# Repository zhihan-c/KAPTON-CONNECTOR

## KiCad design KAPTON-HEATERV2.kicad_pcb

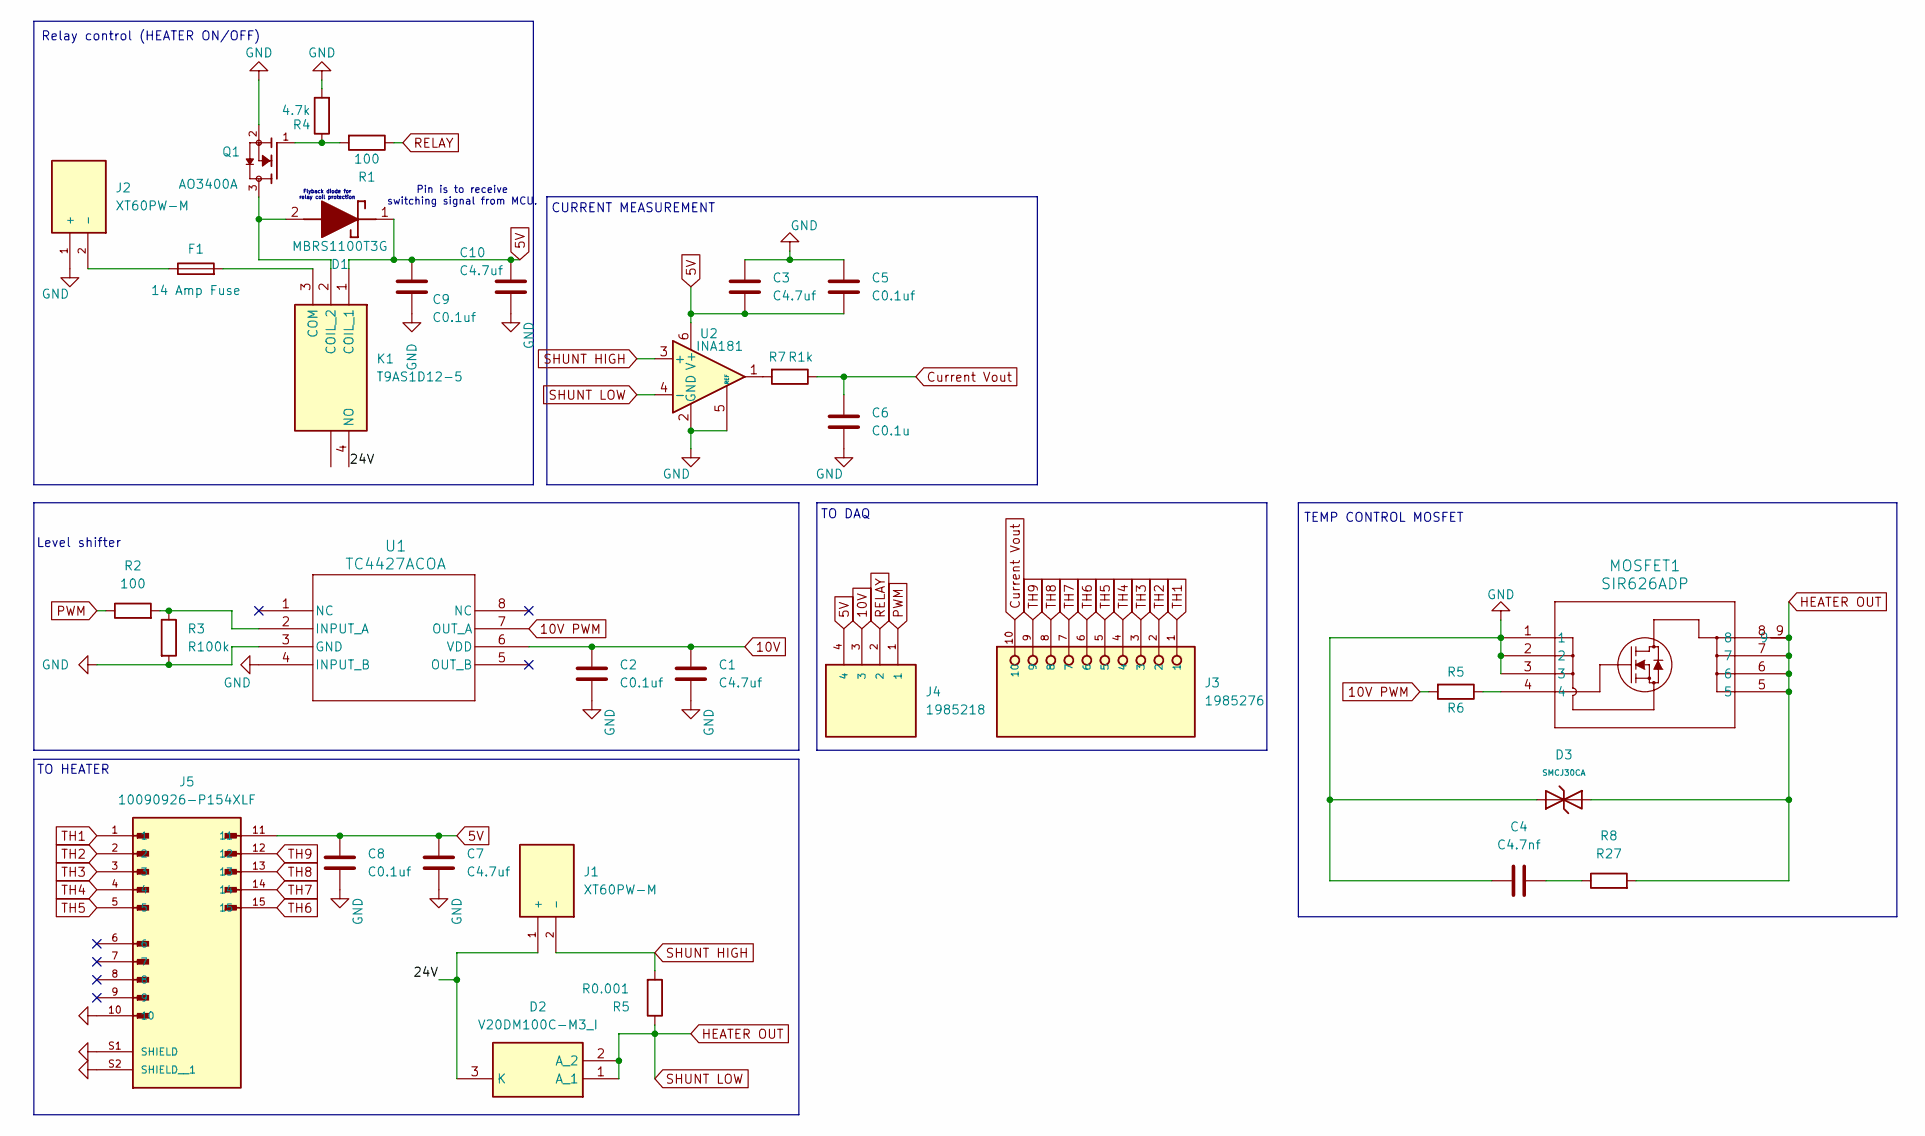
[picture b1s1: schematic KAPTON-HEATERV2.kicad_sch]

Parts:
C1, C3, C7, C10: C4.7uf; C_0805_2012Metric
C2, C5, C8, C9: C0.1uf; C_0805_2012Metric
C4: C4.7nf; CAPC6153X300N
C6: C0.1u; C_0805_2012Metric
D1: MBRS1100T3G; DIOM5436X247N; Mouser Part Number 863-MBRS1100T3G
D2: V20DM100C-M3_I; V40DL45BPM3I; Mouser Part Number 78-V20DM100C-M3/I
D3: SMCJ30CA; D_SMC; Part SMCJ30CA; LCSC C19077607
F1: 14 Amp Fuse; FUSRR508W60L835T400H810
J1, J2: XT60PW-M; AMASS_XT60PW-M; PARTREV V1.2
J3: 1985276; PHOENIX_1985276
J4: 1985218; TE_1985218; PARTREV 29.03.2021
J5: 10090926-P154XLF; AMPHENOL_10090926-P154XLF; PARTREV H
K1: T9AS1D12-5; T9AS1D125; Manufacturer_Part_Number T9AS1D12-5; Mouser Part Number 655-T9AS1D12-5
MOSFET1: SIR626ADP; POWERPAK_SO-8_SINGLE_VIS
Q1: AO3400A; SOT95P280X125-3N; PARTREV L
R1, R2: 100; R_0805_2012Metric
R3: R100k; R_0805_2012Metric
R4: 4.7k; R_0805_2012Metric
R5: R0.001; RESC6432X90N
R6: R5; R_0805_2012Metric
R7: R1k; R_0805_2012Metric
R8: R27; R_1206_3216Metric
U1: TC4427ACOA; SOIC8-N_MC_MCH
U2: INA181; SOT-23-6

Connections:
5V: C3.2, C5.2, C7.1, C8.1, C9.1, C10.1, D1.1 (K), J4.4, J5.11, K1.1 (COIL_1), U2.6 (V+)
10V: C1.1, C2.1, J4.3, U1.6 (VDD)
10V PWM: R6.2, U1.7 (OUT_A)
/24V: D2.3 (K), J1.1 (+), K1.4 (NO)
Current Vout: C6.1, J3.10, R7.1
GND: C1.2, C2.2, C3.1, C4.2, C5.1, C6.2, C7.2, C8.2, C9.2, C10.2, D3.2, J1.S1, J1.S2, J2.1 (+), J2.S1, J2.S2, J5.10, J5.S1 (SHIELD), J5.S2 (SHIELD__1), MOSFET1.1, MOSFET1.2, MOSFET1.3, Q1.2, R3.2, R4.2, U1.3 (GND), U1.4 (INPUT_B), U2.2 (GND), U2.5 (REF)
HEATER OUT: D2.1 (A_1), D2.2 (A_2), D3.1, MOSFET1.5, MOSFET1.6, MOSFET1.7, MOSFET1.8, MOSFET1.9, R5.1, R8.2, U2.4 (-)
unnamed: C4.1, R8.1
unnamed: D1.2 (A), K1.2 (COIL_2), Q1.3
unnamed: F1.1, J2.2 (-)
unnamed: F1.2, K1.3 (COM)
unnamed: MOSFET1.4, R6.1
unnamed: Q1.1, R1.2, R4.1
unnamed: R7.2, U2.1
unnamed: R2.2, R3.1, U1.2 (INPUT_A)
PWM: J4.1, R2.1
RELAY: J4.2, R1.1
SHUNT HIGH: J1.2 (-), R5.2, U2.3 (+)
TH1: J3.1, J5.1
TH2: J3.2, J5.2
TH3: J3.3, J5.3
TH4: J3.4, J5.4
TH5: J3.5, J5.5
TH6: J3.6, J5.15
TH7: J3.7, J5.14
TH8: J3.8, J5.13
TH9: J3.9, J5.12

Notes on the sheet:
TO HEATER
Relay control (HEATER ON/OFF)
TO DAQ
Flyback diode for relay coil protection
CURRENT MEASUREMENT
Level shifter
TEMP CONTROL MOSFET
Pin is to receive switching signal from MCU.

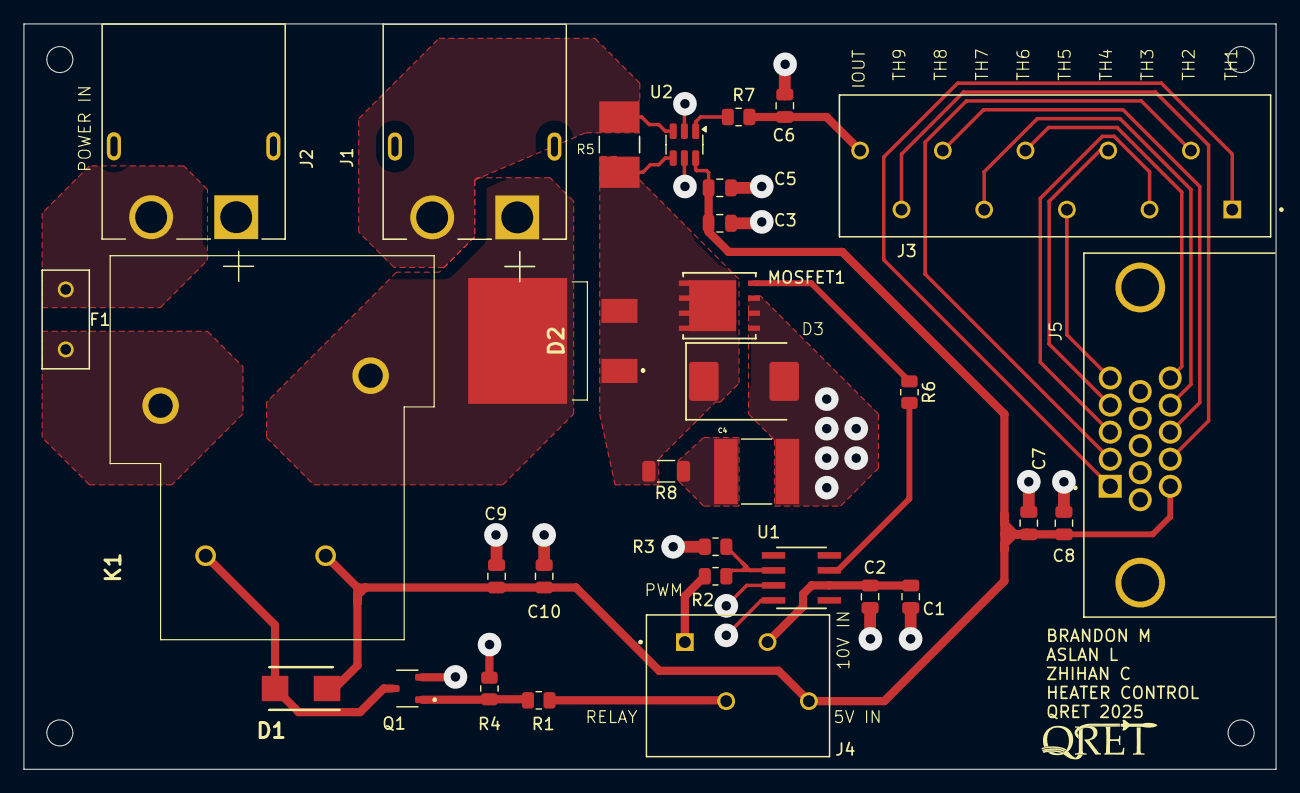
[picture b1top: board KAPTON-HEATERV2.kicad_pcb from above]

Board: 2 copper layers, 106.0 x 63.1 mm, 32 parts (0 on the bottom side), 27 nets.

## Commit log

2025-06-01 added mounting holes
2025-06-03 finalized?
2025-06-04 fixed?
2025-06-04 forgot to save sch
2025-06-04 added resistors to pcb
2025-06-05 fixed a trace
2025-06-05 fixed the mosfet
2025-06-17 added shunt resistor, fixed caps
2025-06-17 edited sch, added footprints
2025-06-18 added current sensing
2025-06-18 working on pcb
2025-06-18 fixed sch
2025-06-18 need to finish netclasses
2025-06-21 iteration 1.2
2025-06-21 trace fix
2025-06-21 fixed DRC issues and made some traces pretty
2025-06-23 copper pour both sides
2025-06-25 June 26 New Traces
2025-06-26 Grounded Shield Connectors J1 J2
2025-06-27 New Relay Footprint
2025-06-27 Rounded to Nearest mm
2025-06-27 Trace Edit and Gerbers
2025-06-27 Updated Gerbers
